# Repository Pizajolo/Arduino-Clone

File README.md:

# Arduino-Clone
Battery powered Arduino clone with clock and extended 512k EEPROM. This board is designed in Kicad.

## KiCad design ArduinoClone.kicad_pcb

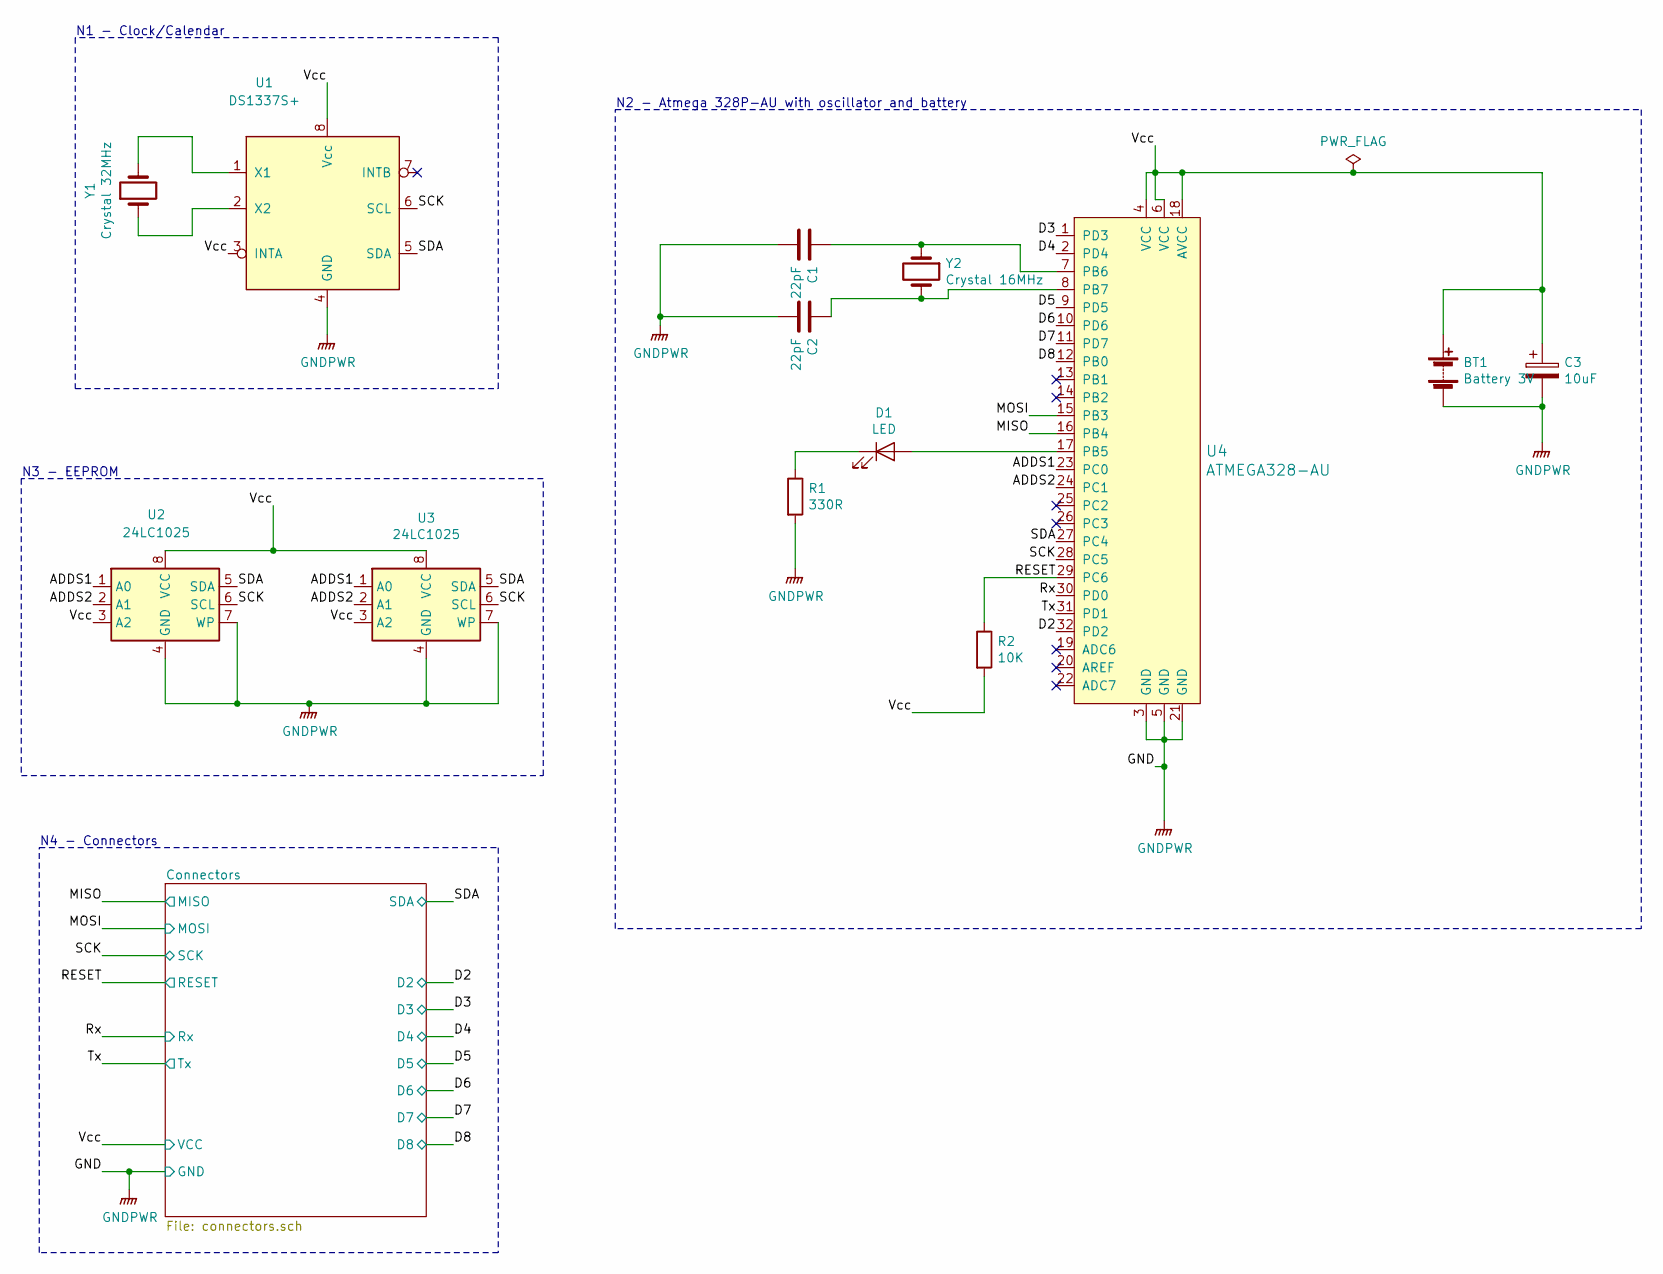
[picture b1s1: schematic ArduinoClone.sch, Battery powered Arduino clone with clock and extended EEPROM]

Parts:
BT1: Battery 3V; PinHeader_1x02_P2.54mm_Vertical
C1, C2: 22pF; C_0805_2012Metric_Pad1.15x1.40mm_HandSolder
C3: 10uF; C_0805_2012Metric_Pad1.15x1.40mm_HandSolder
D1: LED; LED_0805_2012Metric_Pad1.15x1.40mm_HandSolder
R1: 330R; R_0805_2012Metric_Pad1.15x1.40mm_HandSolder
R2: 10K; R_0805_2012Metric_Pad1.15x1.40mm_HandSolder
U1: DS1337S+; SO-8_5.3x6.2mm_P1.27mm
U2, U3: 24LC1025; SOIJ-8_5.3x5.3mm_P1.27mm
U4: ATMEGA328-AU; TQFP-32_7x7mm; MPN ATMEGA328-AU; Digi-Key_PN ATMEGA328-AU-ND
Y1: Crystal 32MHz; Crystal_SMD_MicroCrystal_CC7V-T1A-2Pin_3.2x1.5mm
Y2: Crystal 16MHz; Crystal_SMD_5032-2Pin_5.0x3.2mm_HandSoldering

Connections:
/ADDS1: U2.1 (A0), U3.1 (A0), U4.23 (PC0)
/ADDS2: U2.2 (A1), U3.2 (A1), U4.24 (PC1)
/D2: U4.32 (PD2); also elsewhere on the board
/D3: U4.1 (PD3); also elsewhere on the board
/D4: U4.2 (PD4); also elsewhere on the board
/D5: U4.9 (PD5); also elsewhere on the board
/D6: U4.10 (PD6); also elsewhere on the board
/D7: U4.11 (PD7); also elsewhere on the board
/D8: U4.12 (PB0); also elsewhere on the board
/MISO: U4.16 (PB4); also elsewhere on the board
/MOSI: U4.15 (PB3); also elsewhere on the board
/RESET: R2.1, U4.29 (PC6); also elsewhere on the board
/Rx: U4.30 (PD0); also elsewhere on the board
/SCK: U1.6 (SCL), U2.6 (SCL), U3.6 (SCL), U4.28 (PC5); also elsewhere on the board
/SDA: U1.5 (SDA), U2.5 (SDA), U3.5 (SDA), U4.27 (PC4); also elsewhere on the board
/Tx: U4.31 (PD1); also elsewhere on the board
/Vcc: BT1.1 (+), C3.1, R2.2, U1.3 (INTA), U1.8 (Vcc), U2.3 (A2), U2.8 (VCC), U3.3 (A2), U3.8 (VCC), U4.4 (VCC), U4.6 (VCC), U4.18 (AVCC); also elsewhere on the board
GNDPWR: BT1.2 (-), C1.2, C2.2, C3.2, R1.2, U1.4 (GND), U2.4 (GND), U2.7 (WP), U3.4 (GND), U3.7 (WP), U4.3 (GND), U4.5 (GND), U4.21 (GND); also elsewhere on the board
unnamed: C1.1, U4.7 (PB6), Y2.1
unnamed: C2.1, U4.8 (PB7), Y2.2
unnamed: D1.1 (K), R1.1
unnamed: D1.2 (A), U4.17 (PB5)
unnamed: U1.1 (X1), Y1.2
unnamed: U1.2 (X2), Y1.1

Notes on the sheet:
N1 - Clock/Calendar
N3 - EEPROM
N2 - Atmega 328P-AU with oscillator and battery
N4 - Connectors

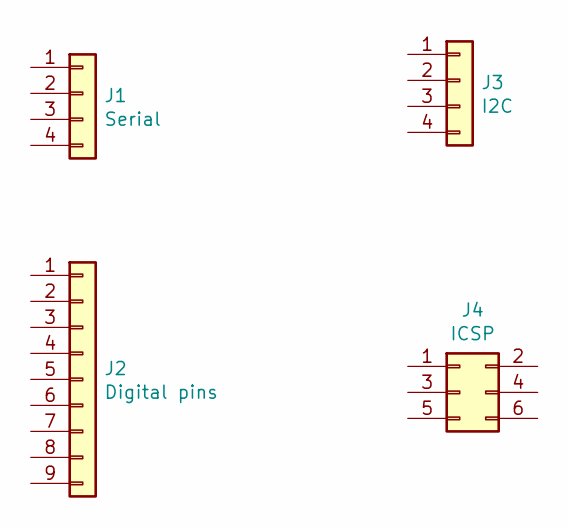
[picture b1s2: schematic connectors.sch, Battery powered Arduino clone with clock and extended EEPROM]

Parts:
J1: Serial; PinSocket_1x04_P2.54mm_Vertical
J2: Digital pins; PinSocket_1x09_P2.54mm_Vertical
J3: I2C; PinSocket_1x04_P2.54mm_Vertical
J4: ICSP; PinSocket_2x03_P2.54mm_Vertical

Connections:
/D2: J2.1; also elsewhere on the board
/D3: J2.2; also elsewhere on the board
/D4: J2.3; also elsewhere on the board
/D5: J2.4; also elsewhere on the board
/D6: J2.5; also elsewhere on the board
/D7: J2.6; also elsewhere on the board
/D8: J2.7; also elsewhere on the board
/MISO: J4.1; also elsewhere on the board
/MOSI: J4.4; also elsewhere on the board
/RESET: J4.5; also elsewhere on the board
/Rx: J1.3; also elsewhere on the board
/SCK: J3.4, J4.3; also elsewhere on the board
/SDA: J3.3; also elsewhere on the board
/Tx: J1.4; also elsewhere on the board
/Vcc: J1.2, J2.9, J3.2, J4.2; also elsewhere on the board
GNDPWR: J1.1, J2.8, J3.1, J4.6; also elsewhere on the board

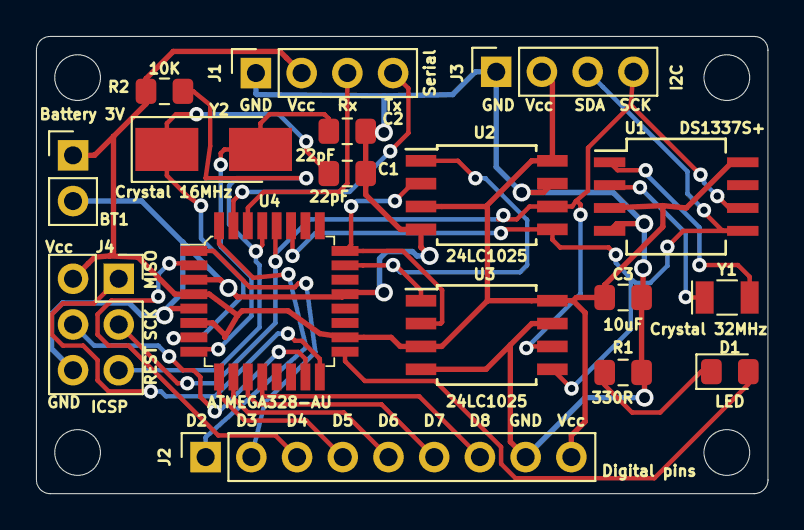
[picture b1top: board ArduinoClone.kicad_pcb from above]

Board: 2 copper layers, 40.6 x 25.4 mm, 17 parts (0 on the bottom side), 24 nets.

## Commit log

2020-04-18 changed Readme
2020-04-18 added kicad files
2020-04-18 added some more files
2020-04-18 added symboles and child sheet
2020-04-18 added new symbol for Atmega328
2020-04-18 created custom Symbol and added it
2020-04-18 Arranged symbols
2020-04-18 Annotated
2020-04-18 added components lables and footprints
2020-04-18 Completed wiring in the connectors sheet
2020-04-18 Completed wiring in the root sheet
2020-04-18 added power flag
2020-04-18 created netlist file
2020-04-19 started work in pcbnew
2020-04-19 added design rules
2020-04-19 corrected error inschematic and placed components in pcbnew
2020-04-19 added edges to board
2020-04-19 routed
2020-04-19 completed Arduino
2020-04-19 final board
2020-04-19 added images
